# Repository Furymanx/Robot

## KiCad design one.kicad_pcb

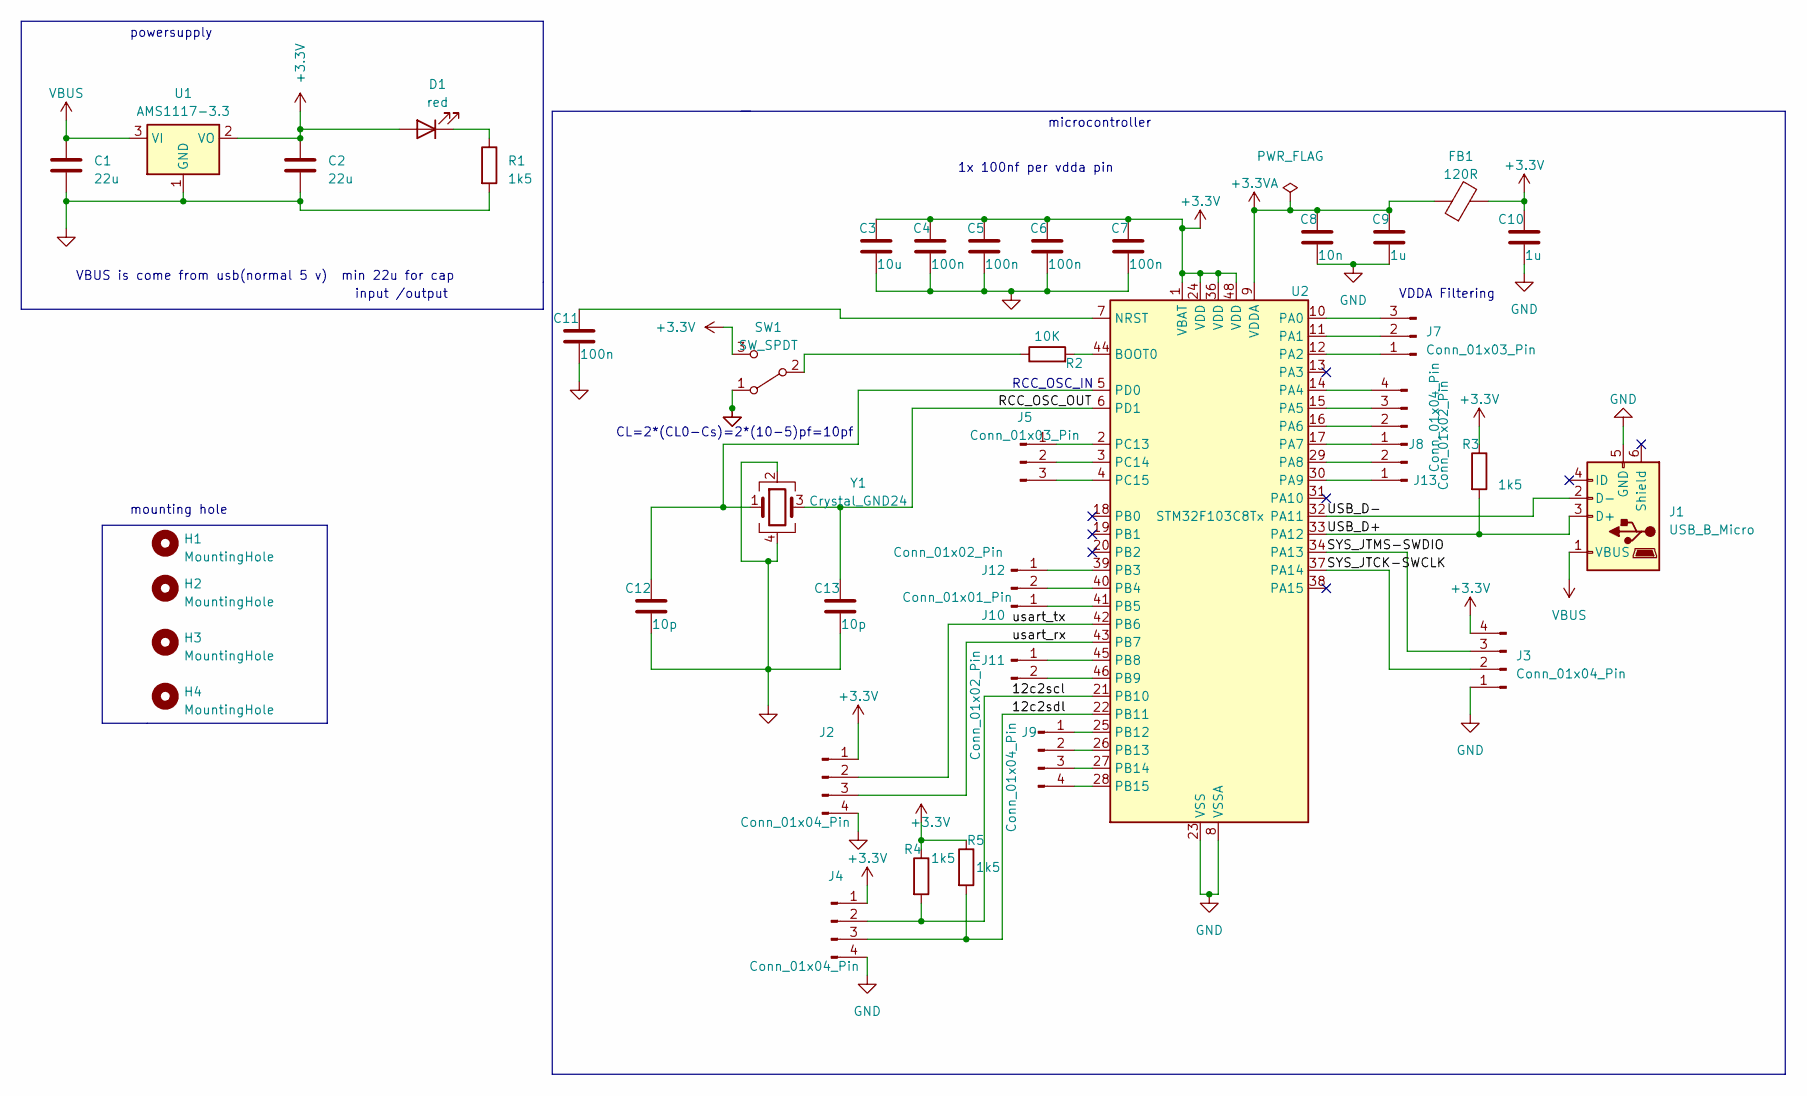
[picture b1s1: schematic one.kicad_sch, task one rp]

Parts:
C1, C2: 22u; C_0805_2012Metric
C3: 10u; C_0603_1608Metric
C4, C5, C6, C7, C11: 100n; C_0402_1005Metric
C8: 10n; C_0402_1005Metric
C9, C10: 1u; C_0402_1005Metric
C12, C13: 10p; C_0402_1005Metric
D1: red; LED_0603_1608Metric
FB1: 120R; L_0603_1608Metric
H1, H2, H3, H4: MountingHole; MountingHole_2.2mm_M2
J1: USB_B_Micro; USB_Micro-B_Wuerth_629105150521
J2, J3, J4, J8, J9: Conn_01x04_Pin; PinHeader_1x04_P2.54mm_Vertical
J5, J7: Conn_01x03_Pin; PinHeader_1x03_P2.54mm_Vertical
J10: Conn_01x01_Pin; PinHeader_1x01_P2.54mm_Vertical
J11, J12, J13: Conn_01x02_Pin; PinHeader_1x02_P2.54mm_Vertical
R1, R3, R4, R5: 1k5; R_0402_1005Metric
R2: 10K; R_0402_1005Metric
SW1: SW_SPDT; SW_SPDT_PCM12
U1: AMS1117-3.3; SOT-223-3_TabPin2
U2: STM32F103C8Tx; LQFP-48_7x7mm_P0.5mm
Y1: Crystal_GND24; Crystal_SMD_3225-4Pin_3.2x2.5mm

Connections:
+3.3V: C2.1, C3.1, C4.1, C5.1, C6.1, C7.1, C10.1, D1.2 (A), FB1.2, J2.1, J3.4, J4.1, R3.1, R4.1, R5.1, SW1.3 (C), U1.2 (VO), U2.1 (VBAT), U2.24 (VDD), U2.36 (VDD), U2.48 (VDD)
+3.3VA: C8.1, C9.1, FB1.1, U2.9 (VDDA)
/12c2scl: J4.2, R4.2, U2.21 (PB10)
/12c2sdl: J4.3, R5.2, U2.22 (PB11)
/RCC_OSC_OUT: C13.1, U2.6 (PD1), Y1.3
/SYS_JTCK-SWCLK: J3.2, U2.37 (PA14)
/SYS_JTMS-SWDIO: J3.3, U2.34 (PA13)
/USB_D+: J1.3 (D+), R3.2, U2.33 (PA12)
/USB_D-: J1.2 (D-), U2.32 (PA11)
/usart_rx: J2.3, U2.43 (PB7)
/usart_tx: J2.2, U2.42 (PB6)
GND: C1.2, C2.2, C3.2, C4.2, C5.2, C6.2, C7.2, C8.2, C9.2, C10.2, C11.2, C12.2, C13.2, J1.5 (GND), J2.4, J3.1, J4.4, R1.2, SW1.1 (A), U1.1 (GND), U2.8 (VSSA), U2.23 (VSS), U2.35 (VSS), U2.47 (VSS), Y1.2, Y1.4
unnamed: D1.1 (K), R1.1
unnamed: J5.1, U2.2 (PC13)
unnamed: J5.2, U2.3 (PC14)
unnamed: J5.3, U2.4 (PC15)
unnamed: J7.1, U2.12 (PA2)
unnamed: J7.2, U2.11 (PA1)
unnamed: J7.3, U2.10 (PA0)
unnamed: J8.1, U2.17 (PA7)
unnamed: J8.2, U2.16 (PA6)
unnamed: J8.3, U2.15 (PA5)
unnamed: J8.4, U2.14 (PA4)
unnamed: J9.1, U2.25 (PB12)
unnamed: J9.2, U2.26 (PB13)
unnamed: J9.3, U2.27 (PB14)
unnamed: J9.4, U2.28 (PB15)
unnamed: J10.1, U2.41 (PB5)
unnamed: J11.1, U2.45 (PB8)
unnamed: J11.2, U2.46 (PB9)
unnamed: J12.1, U2.39 (PB3)
unnamed: J12.2, U2.40 (PB4)
unnamed: J13.1, U2.30 (PA9)
unnamed: J13.2, U2.29 (PA8)
unnamed: R2.1, SW1.2 (B)
unnamed: R2.2, U2.44 (BOOT0)
unnamed: C11.1, U2.7 (NRST)
unnamed: C12.1, U2.5 (PD0), Y1.1
VBUS: C1.1, J1.1 (VBUS), U1.3 (VI)

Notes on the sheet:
VBUS is come from usb(normal 5 v) min 22u for cap
powersupply
CL=2*(CL0-Cs)=2*(10-5)pf=10pf
microcontroller
input /output
VDDA Filtering
1x 100nf per vdda pin
mounting hole
RCC_OSC_IN

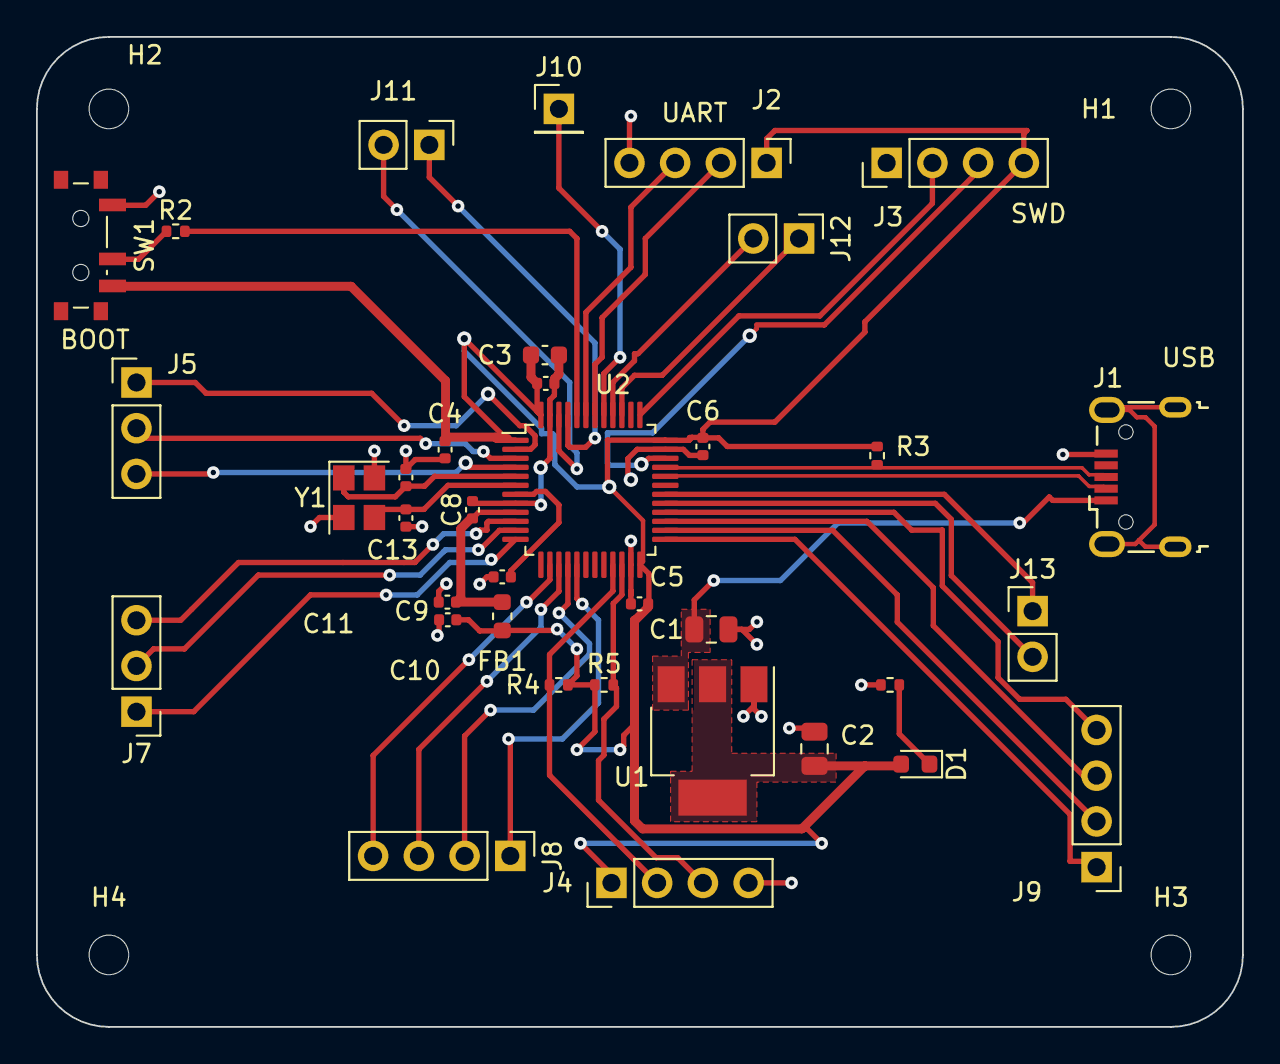
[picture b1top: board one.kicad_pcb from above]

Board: 2 copper layers, 67.0 x 55.0 mm, 40 parts (0 on the bottom side), 39 nets.
